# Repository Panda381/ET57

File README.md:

# ET57
Clone of TI-57 calculator with ATmega8 processor.

(c) 2020 Miroslav Nemecek, Panda38@seznam.cz

open source

Translation of manuals into English and French: Pierre Houbert http://pierre.phweb.me

Last update: 1.11.2020, build 201101

project home web page: https://www.breatharian.eu/hw/et57/index_en.html

ET-57 on GitHub: https://github.com/Panda381/ET57

Description
-----------
The ET-57 calculator was created as an effort to fit a fully functional programmable calculator into the 8 KB memory of the ATmega8 processor. The popular TI-57 calculator from Texas Instruments from 1977 was chosen as a model. This is not a replica with processor emulation, but an independent new firmware based on the functionality of the original calculator. The calculator could be expanded with more memory and more functions without compromising compatibility with the original. Programs for the TI-57 can usually be run in the ET-57 calculator without the need for modifications.

The ET-57 calculator is intended for those interested in retro technology and also as a teaching aid for school clubs, thanks to its ease of use, economical coding of programs, low price, support for external peripherals and fully open code.

The ET-57 calculator software is also available for the ET-58 calculator hardware, as an ET-57B variant. https://www.breatharian.eu/hw/et58/index_en.html

Properties
----------
- ATmega8 processor (8MHz, 8KB ROM, 1KB RAM, 512B EEPROM)
- 5 V supply voltage (from USB charger or from USB port)
- Calculations in BCD code
- Accuracy of calculations 17 digits
- Accuracy of basic registers 15 digits
- Accuracy of extended registers 13 digits
- Display data at 11 significant digits
- Exponent 2 digits, range + - 99
- 10 program spaces
- Each space 50 program steps (total 500 steps)
- User program stored in EEPROM (without battery)
- 10 basic registers (accessible by direct addressing)
- 70 extended registers (accessible by index addressing)
- Two-line LCD display (2 x 16 alphanumeric characters)
- 40 buttons
- Control of external devices via ISP connector
- Calculator code completely written in AVR assembler
- Exponential and logarithmic functions
- Trigonometric functions
- Factorial
- Random number generator
- Index access to variables
- Scientific display mode with exponent
- Statistical function
- 10 labels in each program space
- Function calls and jumps between program spaces
- Fully open source hardware and software

Diagram
-------
The USB connector is only used to power +5V the calculator from an external charger or USB port. The processor uses an internal 8 MHz RC oscillator. Resistor R2 is used to limit the LED current for the display backlight. With this variant of the display, it is probably possible to omit and connect directly to GND (not verified). Resistor R3 regulates the bias voltage for the display contrast. It may be necessary to change to a different value for another display.

Construction
------------
For maximum simplification of the construction, microswitches without a fingerboard were used as buttons, only protruding above the surface of the calculator. The display is soldered via a pin strip. The printed circuit board was chosen to be 10x7.5 cm because it is both available from GM and meets the board size limit for the free Eagle version. The printed circuit board is sufficient on one side, supplemented by 5 wire jumpers. The construction was chosen "sandwich" for simplicity - from above and below the printed circuit board is screwed to the plexiglass boards. But they are not necessary and the calculator can be easily operated even without a cover - it is enough to place a paper template with button labels over the buttons.

The display was chosen with pins on the bottom to make do with a smaller printed circuit board (and also because I had a supply of these displays). I list a similar display in the parts list (I did not find the original one), but its suitability for replacement has not been verified, it must be verified. E.g. there may be a different order of pins for LED illumination - my display has the opposite numbering 15 and 16, but as a result the pins appear to be the same on the printed circuit board.

Be careful when attaching wire to pin 8 of the ISP connector, it could touch the display cover plate. It is therefore guided by an arc. The display is soldered via a pin strip. Before soldering the pin on the display, press it from top to bottom (as far as it will go) so that it does not obstruct the cover. Although I soldered the ISP programming connector from the display side, it may be more practical to solder from the PCB side, because the display of the connector interferes a bit.

The label of the buttons can be glued to the cover or just placed over the buttons. The holes for the buttons are punched through the intersection of 4 mm on the skin. Printed paper can be coated with laminating foil or transparent double-sided insulating tape.

A hole for the USB power connector needs to be cut in the bottom cover. It might also be useful to cut a hole for the ISP programming connector (it is also used to connect peripherals).

Firmware programming
--------------------
The firmware includes source code in the AVR assembler (compiled with WinAVR) and compiled HEX files for the ET-57 variant with ATmega8 processor, and files for the ET-57B variant (ET-58 hardware) with ATmega88, ATmega168 or ATmega328 processor.

ATmega8 processor fuse settings (for ET-57 hardware): low E4, high D1.

For hardware ET-58, ATmega88: low 42, high D6, ext F9, ATmega168: low 42, high D6, ext F9, ATmega328: low 42, high D1, ext FE.

An 8-pin KONPC-SPK-8 busbar with the following pin assignment is used as the ISP connector:

1 SCK

2 MISO

3 MOSI

4 orientation key (pin missing, blinded in the connector so that it cannot be inserted)

5 /RESET

6 GND (ground, 0V)

7 VCC (power,+5V)

8 not used

External device and ports
-------------------------
The calculator allows the connection of external peripherals via the ISP connector, with the SPI protocol. As an example, the LED control on the ERAM100 effects frame (ATmega8 processor) is shown here.

Used components
---------------
Note: The LCD display shown here is not verified if it works with the specified connection and was selected only by similarity.

958-174, 1 piece, ATMEGA8A-AU TQFP32 ATMEL, 66 Kc https://www.gme.cz/atmega8a-au-tqfp32-atmel

513-219, 1 piece, LCD alfanumeric display 2x16 haracters, green WH1602A-YGH-CT, 139 Kc https://www.gme.cz/lcd-alfanumericky-displej-winstar-wh1602a-ygh-ct

832-177, 1 piece, Connector USB-MINI B F SMD, 17 Kc https://www.gme.cz/usb-konektor-usb-mini-b-f-smd

630-158, 40 pieces, Microswitch TC-0108-T, 2.80 Kc (10 ks 2.11) ... 84.40 Kc https://www.gme.cz/tc-0108-t

832-017, 1 piece, Pin rail S1G20 2,54mm, 3.60 Kc https://www.gme.cz/oboustranny-kolik-s1g20-2-54mm

832-470, 1 piece, Pin rail S1G08W 2,54mm, 2.30 Kc https://www.gme.cz/oboustranny-kolik-s1g08w-2-54mm

906-096, 1 piece, Ceramic capacitor CKS0805 100n/50V X7R 10%, 5.50 Kc https://www.gme.cz/cks0805-100n-50v-x7r-10-yageo

906-089, 1 piece, Ceramic capacitor CKS0805 10n/50V X7R 10% YAGEO, 2.20 Kc https://www.gme.cz/cks0805-10n-50v-x7r-10-yageo

901-029, 2 pieces, SMD Resistor R0805 1k0 5%, 0.68 Kc ... 1.36 Kc https://www.gme.cz/r0805-1k0-5-yageo

901-573, 1 piece, SMD Resistor R0805 15R 1%, 2.50 Kc https://www.gme.cz/r0805-15r-1-yageo

661-073, 1 piece, Fotocuprextit 75x100x1,5 one-sided, 39 Kc https://www.gme.cz/fotocuprextit-75x100x1-5-jednovrstvy

Sum of the price for all 324 CZK (without photocuprextite and without cover).

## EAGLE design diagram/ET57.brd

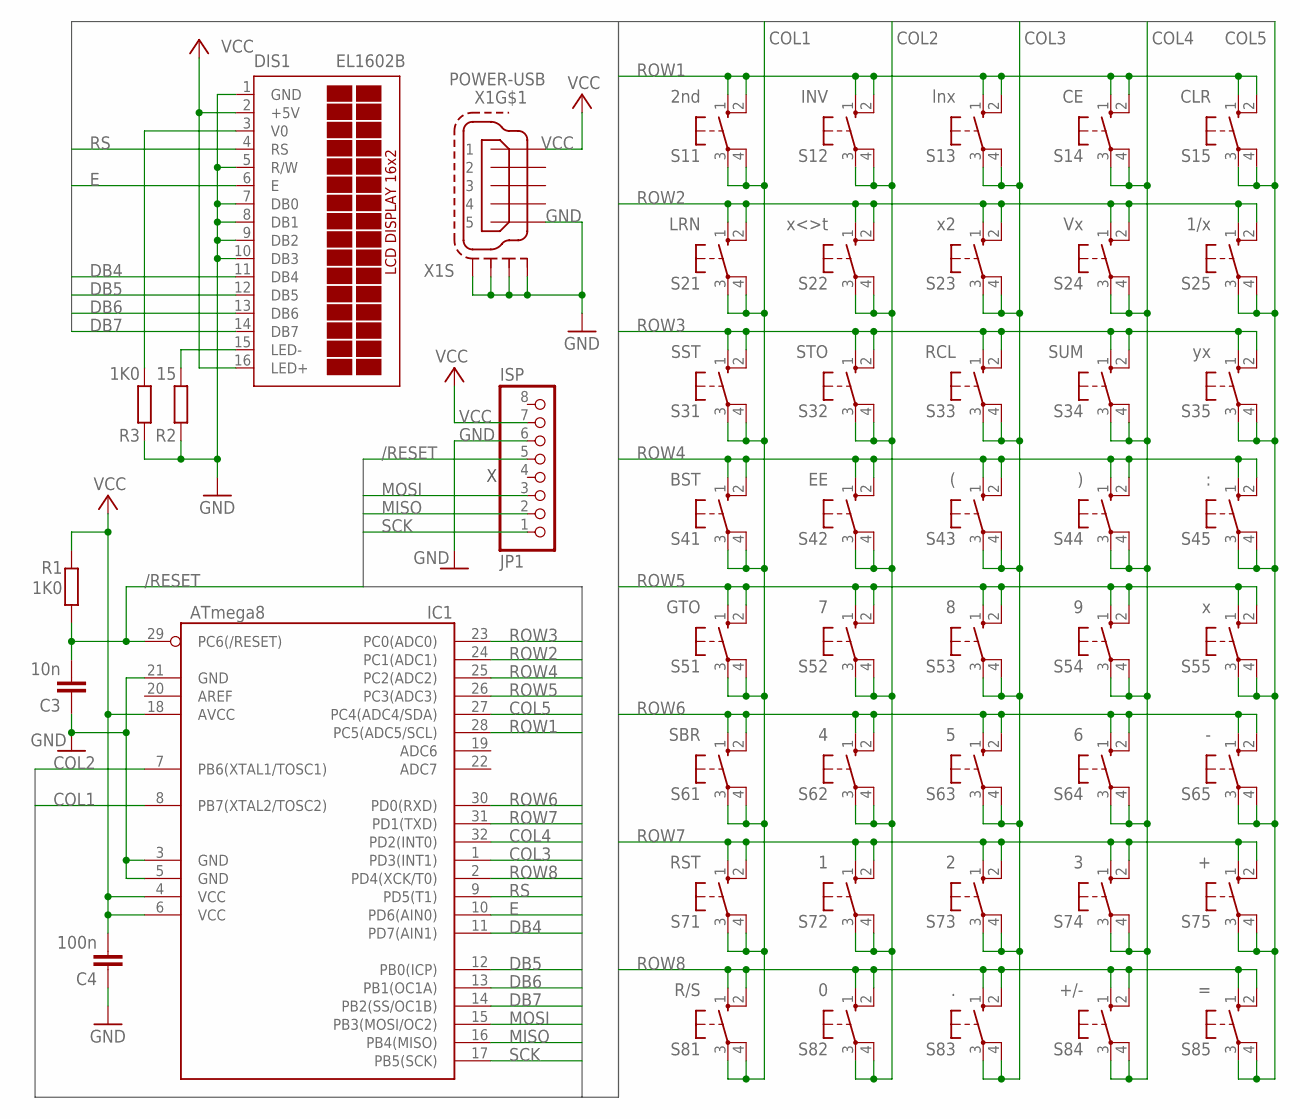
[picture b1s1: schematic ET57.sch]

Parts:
C3: 10n; C0805
C4: 100n; C0805
DIS1: EL1602B
IC1: ATmega8; TQFP32-08
JP1: ISP; 1X08-BIG
R1, R3: 1K0; R0805
R2: 15; R0805
S11: 2nd; B3F-10XX
S12: INV; B3F-10XX
S13: lnx; B3F-10XX
S14: CE; B3F-10XX
S15: CLR; B3F-10XX
S21: LRN; B3F-10XX
S22: x<>t; B3F-10XX
S23: x2; B3F-10XX
S24: Vx; B3F-10XX
S25: 1/x; B3F-10XX
S31: SST; B3F-10XX
S32: STO; B3F-10XX
S33: RCL; B3F-10XX
S34: SUM; B3F-10XX
S35: yx; B3F-10XX
S41: BST; B3F-10XX
S42: EE; B3F-10XX
S43: (; B3F-10XX
S44: ); B3F-10XX
S45: :; B3F-10XX
S51: GTO; B3F-10XX
S52: 7; B3F-10XX
S53: 8; B3F-10XX
S54: 9; B3F-10XX
S55: x; B3F-10XX
S61: SBR; B3F-10XX
S62: 4; B3F-10XX
S63: 5; B3F-10XX
S64: 6; B3F-10XX
S65: -; B3F-10XX
S71: RST; B3F-10XX
S72: 1; B3F-10XX
S73: 2; B3F-10XX
S74: 3; B3F-10XX
S75: +; B3F-10XX
S81: R/S; B3F-10XX
S82: 0; B3F-10XX
S83: .; B3F-10XX
S84: +/-; B3F-10XX
S85: =; B3F-10XX
X1: POWER-USB; 32005-201

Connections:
/RESET: C3.2, IC1.29 (PC6(/RESET)), JP1.5, R1.1
COL1: IC1.8 (PB7(XTAL2/TOSC2)), S11.3, S11.4 (P1), S21.3, S21.4 (P1), S31.3, S31.4 (P1), S41.3, S41.4 (P1), S51.3, S51.4 (P1), S61.3, S61.4 (P1), S71.3, S71.4 (P1), S81.3, S81.4 (P1)
COL2: IC1.7 (PB6(XTAL1/TOSC1)), S12.3, S12.4 (P1), S22.3, S22.4 (P1), S32.3, S32.4 (P1), S42.3, S42.4 (P1), S52.3, S52.4 (P1), S62.3, S62.4 (P1), S72.3, S72.4 (P1), S82.3, S82.4 (P1)
COL3: IC1.1 (PD3(INT1)), S13.3, S13.4 (P1), S23.3, S23.4 (P1), S33.3, S33.4 (P1), S43.3, S43.4 (P1), S53.3, S53.4 (P1), S63.3, S63.4 (P1), S73.3, S73.4 (P1), S83.3, S83.4 (P1)
COL4: IC1.32 (PD2(INT0)), S14.3, S14.4 (P1), S24.3, S24.4 (P1), S34.3, S34.4 (P1), S44.3, S44.4 (P1), S54.3, S54.4 (P1), S64.3, S64.4 (P1), S74.3, S74.4 (P1), S84.3, S84.4 (P1)
COL5: IC1.27 (PC4(ADC4/SDA)), S15.3, S15.4 (P1), S25.3, S25.4 (P1), S35.3, S35.4 (P1), S45.3, S45.4 (P1), S55.3, S55.4 (P1), S65.3, S65.4 (P1), S75.3, S75.4 (P1), S85.3, S85.4 (P1)
DB4: DIS1.11 (DB4), IC1.11 (PD7(AIN1))
DB5: DIS1.12 (DB5), IC1.12 (PB0(ICP))
DB6: DIS1.13 (DB6), IC1.13 (PB1(OC1A))
DB7: DIS1.14 (DB7), IC1.14 (PB2(SS/OC1B))
E: DIS1.6 (E), IC1.10 (PD6(AIN0))
GND: C3.1, C4.1, DIS1.1 (GND), DIS1.5 (R/W), DIS1.7 (DB0), DIS1.8 (DB1), DIS1.9 (DB2), DIS1.10 (DB3), IC1.3 (GND), IC1.5 (GND), IC1.21 (GND), JP1.6, R2.1, R3.1, X1.5, X1.M1 (S1), X1.M2 (S2), X1.M3 (S3), X1.M4 (S4)
MISO: IC1.16 (PB4(MISO)), JP1.2
MOSI: IC1.15 (PB3(MOSI/OC2)), JP1.3
unnamed: DIS1.15 (LED-), R2.2
unnamed: DIS1.3 (V0), R3.2
ROW1: IC1.28 (PC5(ADC5/SCL)), S11.1 (S), S11.2 (S1), S12.1 (S), S12.2 (S1), S13.1 (S), S13.2 (S1), S14.1 (S), S14.2 (S1), S15.1 (S), S15.2 (S1)
ROW2: IC1.24 (PC1(ADC1)), S21.1 (S), S21.2 (S1), S22.1 (S), S22.2 (S1), S23.1 (S), S23.2 (S1), S24.1 (S), S24.2 (S1), S25.1 (S), S25.2 (S1)
ROW3: IC1.23 (PC0(ADC0)), S31.1 (S), S31.2 (S1), S32.1 (S), S32.2 (S1), S33.1 (S), S33.2 (S1), S34.1 (S), S34.2 (S1), S35.1 (S), S35.2 (S1)
ROW4: IC1.25 (PC2(ADC2)), S41.1 (S), S41.2 (S1), S42.1 (S), S42.2 (S1), S43.1 (S), S43.2 (S1), S44.1 (S), S44.2 (S1), S45.1 (S), S45.2 (S1)
ROW5: IC1.26 (PC3(ADC3)), S51.1 (S), S51.2 (S1), S52.1 (S), S52.2 (S1), S53.1 (S), S53.2 (S1), S54.1 (S), S54.2 (S1), S55.1 (S), S55.2 (S1)
ROW6: IC1.30 (PD0(RXD)), S61.1 (S), S61.2 (S1), S62.1 (S), S62.2 (S1), S63.1 (S), S63.2 (S1), S64.1 (S), S64.2 (S1), S65.1 (S), S65.2 (S1)
ROW7: IC1.31 (PD1(TXD)), S71.1 (S), S71.2 (S1), S72.1 (S), S72.2 (S1), S73.1 (S), S73.2 (S1), S74.1 (S), S74.2 (S1), S75.1 (S), S75.2 (S1)
ROW8: IC1.2 (PD4(XCK/T0)), S81.1 (S), S81.2 (S1), S82.1 (S), S82.2 (S1), S83.1 (S), S83.2 (S1), S84.1 (S), S84.2 (S1), S85.1 (S), S85.2 (S1)
RS: DIS1.4 (RS), IC1.9 (PD5(T1))
SCK: IC1.17 (PB5(SCK)), JP1.1
VCC: C4.2, DIS1.2 (+5V), DIS1.16 (LED+), IC1.4 (VCC), IC1.6 (VCC), IC1.18 (AVCC), JP1.7, R1.2, X1.1

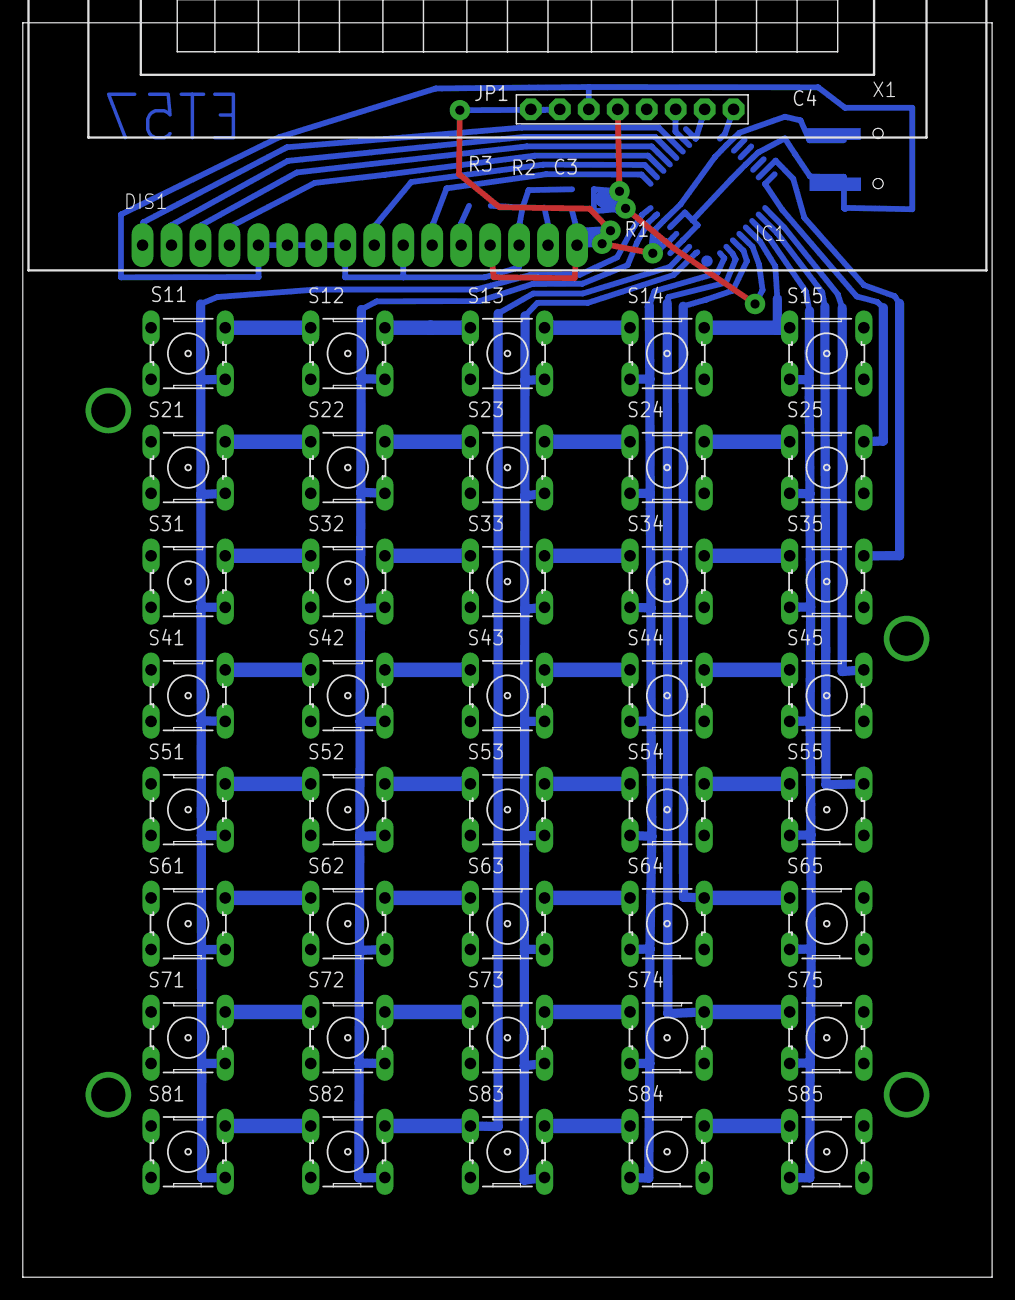
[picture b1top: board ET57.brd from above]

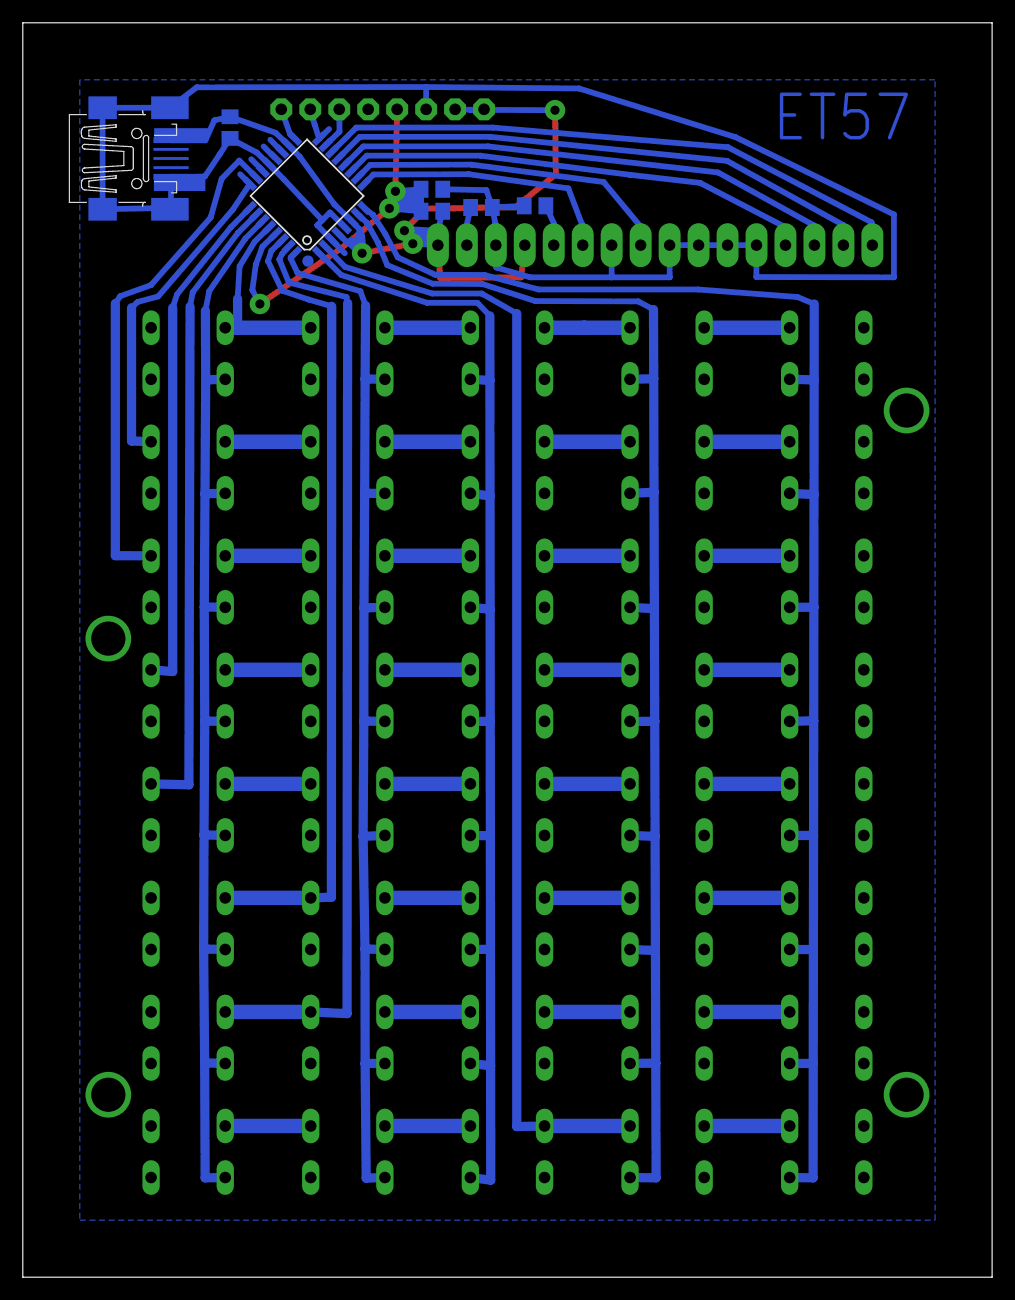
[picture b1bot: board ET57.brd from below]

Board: 2 copper layers, 85.0 x 110.0 mm, 49 parts (7 on the bottom side), 27 nets.

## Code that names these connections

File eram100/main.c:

// =============================================================================
//                                 
//                           LED frame ERAM100
//
// =============================================================================

#include "include.h"

// SPI slave data
u8 SPIData[SPIDATA_MAX];

// index of SPI command
u8 SPIInx;

// SPI command
u8 SPICmd;	// 1st byte - SPI command
u8 SPIAddr;	// 2nd byte - SPI address

// ports to TPIC6B595:
//   PD5 (9) ... DDT ... SERIN (3)
//   PD6 (10) ... SCLK ... CLOCK (13)
//   PD7 (11) ... STB ... STB (12)
//   PB1 (13) ... /OE ... /OE (9)

// output all LEDs
void SetAll(u8 led)
{
	u8 i;

	// loop through 8 LEDs
	for (i = 8; i > 0; i--)
	{
		// output data bit SERIN
		if (led & BIT(7))
			PORTD |= B5;
		else
			PORTD &= ~B5;

		// shift LED register
		led <<= 1;

		// pulse clock SCLK
		PORTD |= B6;
		PORTD &= ~B6;
	}

	// strobe data to output register STB
	PORTD |= B7;
	PORTD &= ~B7;
}

// SPI init (Slave mode)
void SPI_SlaveInit()
{
	// reset SPI index
	SPIInx = 0;

	// enable SPI in slave mode (MSB first, sampled on leading edge, leading edge is rising)
	//  B0,B1 (SPR0, SPR1): SCK clock rate (Master mode) ... and SPI2X bit of SPSR too
	//  B2 (CPHA): clock phase, sampled 0=leading edge, 1=trailing edge
	//  B3 (CPOL): clock polarity, leading edge 0=rising, 1=falling
	//  B4 (MSTR): select mode 0=slave, 1=master
	//  B5 (DORD): data order 0=MSB first, 1=LSB first
	//  B6 (SPE): 1=SPI enabled
	//  B7 (SPIE): 1=SPI interrupt enable
	SPCR = BIT(SPE) | BIT(SPIE);
}

// SPI terminate
void SPI_Term()
{
	// SPI disable
	SPCR = 0;

	// flush flags
	volatile u8 k = SPSR;
	k = SPDR;
}

// SPI interrupt
ISR(SPI_STC_vect)
{
	// read data byte
	u8 d = SPDR;

	// receive command
	if (SPIInx == 0)
	{
		// check known commands
		if (	(d != SPICMD_SYNC) &&
			(d != SPICMD_READ) &&
			(d != SPICMD_WRITE))
		{
			// error, try to re-synchronize
			SPDR = SPICMD_ERR; // report error to master
			SPI_Term(); // terminate SPI
			_delay_us(50); // short delay 50 us (master delays 100 us after syncerror)
			SPI_SlaveInit(); // re-initialize SPI
			return;
		}

		// shift to next byte of the command
		if (d != SPICMD_SYNC)
		{
			SPICmd = d;
			SPIInx = 1; // next index = address
		}
	}

	// receive address
	else if (SPIInx == 1)
	{
		SPIAddr = d; // save address
		SPIInx = 2; // next index = data

		// read data
		if (SPICmd == SPICMD_READ) SPDR = SPIData[d];
	}

	// receive data
	else
	{
		// next index = command
		SPIInx = 0;

		// write data
		if (SPICmd == SPICMD_WRITE) SPIData[SPIAddr] = d;
	}
}

// main function
int main(void)
{
	// set port B
	//  PB5: SCK, input from SPI, pull-up
	//  PB4: MISO, output to SPI, LOW
	//  PB3: MOSI, input from SPI, pull-up
	//  PB2: SS, input connected to GND
	//  PB1: /OE, output LOW
	DDRB = B4 + B1; // set outputs
	PORTB = B5 + B3; // set pull-ups

	// set port D
	//  PD7: STB, output to TPIC6B595, LOW
	//  PD6: SCLK, output to TPIC6B595, LOW
	//  PD5: SERIN, output to TPIC6B595, LOW
	DDRD = B7 + B6 + B5; // set outpus
	PORTD = 0; // set LOWs

	// clear slave data
	u16 i;
	for (i = 0; i < SPIDATA_MAX; i++) SPIData[i] = 0;

	// interrupt enable
	sei();

	// SPI init (Slave mode)
	SPI_SlaveInit();

	while (1)
	{
		// set all LEDs
		SetAll(SPIData[0]);
//		_delay_ms(100);
	}
}
